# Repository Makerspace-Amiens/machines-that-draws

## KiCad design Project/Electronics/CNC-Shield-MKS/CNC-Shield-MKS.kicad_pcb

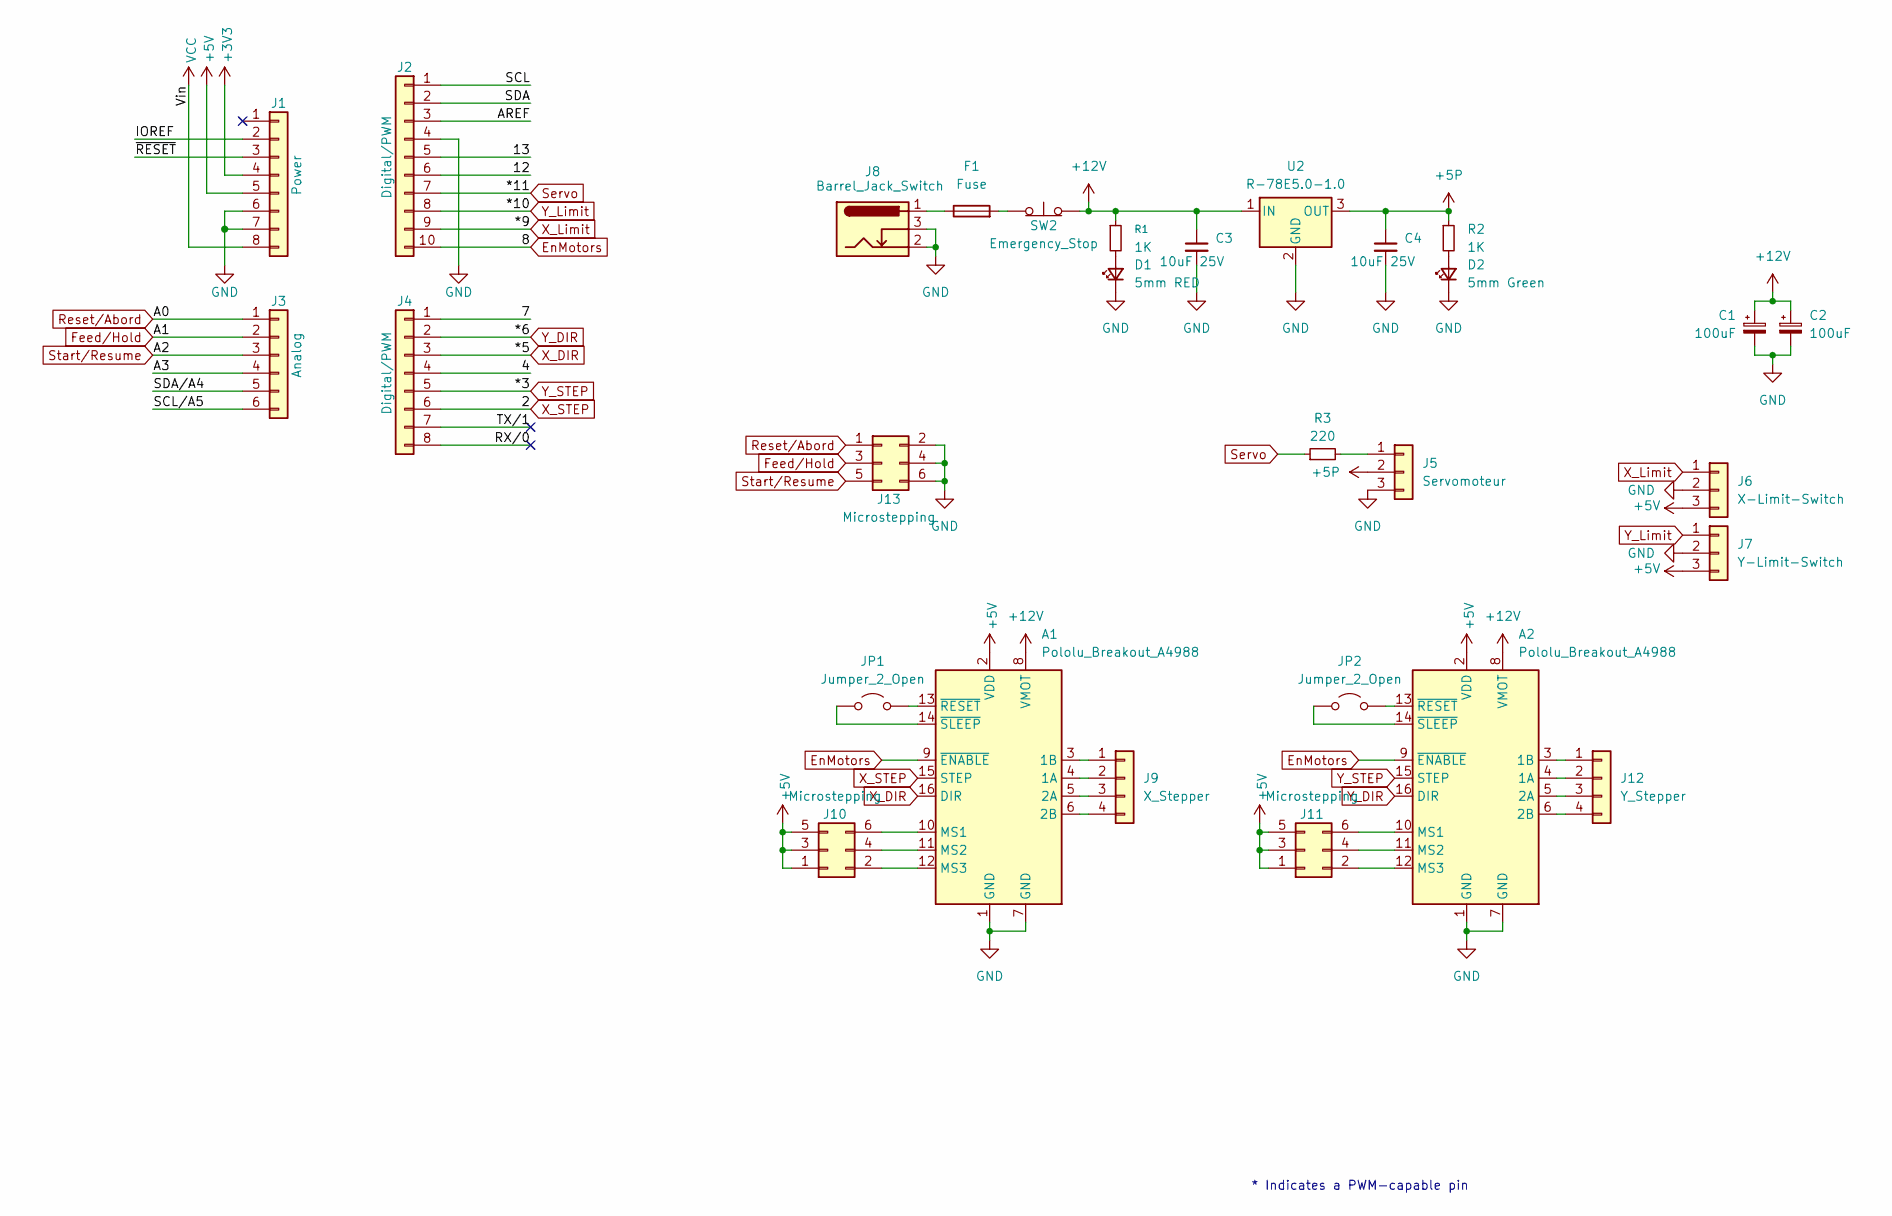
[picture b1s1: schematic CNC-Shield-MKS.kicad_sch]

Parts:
A1, A2: Pololu_Breakout_A4988; Pololu_Breakout-16_15.2x20.3mm
C1, C2: 100uF; CP_Radial_D8.0mm_P3.50mm
C3, C4: 10uF 25V; C_Disc_D6.0mm_W2.5mm_P5.00mm
D1: 5mm RED; LED_D5.0mm
D2: 5mm Green; LED_D5.0mm
F1: Fuse; Fuseholder_Blade_Mini_Keystone_3568
J1: Power; PinHeader_1x08_P2.54mm_Vertical
J2: Digital/PWM; PinHeader_1x10_P2.54mm_Vertical
J3: Analog; PinHeader_1x06_P2.54mm_Vertical
J4: Digital/PWM; PinHeader_1x08_P2.54mm_Vertical
J5: Servomoteur; PinHeader_1x03_P2.54mm_Vertical
J6: X-Limit-Switch; PinHeader_1x03_P2.54mm_Vertical
J7: Y-Limit-Switch; PinHeader_1x03_P2.54mm_Vertical
J8: Barrel_Jack_Switch; BarrelJack_Horizontal
J9: X_Stepper; PinHeader_1x04_P2.54mm_Vertical
J10, J11, J13: Microstepping; PinHeader_2x03_P2.54mm_Vertical
J12: Y_Stepper; PinHeader_1x04_P2.54mm_Vertical
JP1, JP2: Jumper_2_Open; TestPoint_2Pads_Pitch2.54mm_Drill0.8mm
R1, R2: 1K; R_Axial_DIN0204_L3.6mm_D1.6mm_P5.08mm_Horizontal
R3: 220; R_Axial_DIN0204_L3.6mm_D1.6mm_P5.08mm_Horizontal
SW2: Emergency_Stop; TerminalBlock_Phoenix_MKDS-1,5-2_1x02_P5.00mm_Horizontal
U2: R-78E5.0-1.0; Converter_DCDC_RECOM_R-78E-0.5_THT

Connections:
+3V3: J1.4
+5P: C4.1, J5.2, R2.1, U2.3 (OUT)
+5V: A1.2 (VDD), A2.2 (VDD), J1.5, J6.3, J7.3, J10.1, J10.3, J10.5, J11.1, J11.3, J11.5
+12V: A1.8 (VMOT), A2.8 (VMOT), C1.1, C2.1, C3.1, R1.1, SW2.1 (A), U2.1 (IN)
/4: J4.4
/7: J4.1
/12: J2.6
/13: J2.5
/A3: J3.4
/AREF: J2.3
/IOREF: J1.2
/RX/0: J4.8
/SCL: J2.1
/SCL/A5: J3.6
/SDA: J2.2
/SDA/A4: J3.5
/TX/1: J4.7
/~RESET: J1.3
EnMotors: A1.9 (~ENABLE), A2.9 (~ENABLE), J2.10
Feed/Hold: J3.2, J13.3
GND: A1.1 (GND), A1.7 (GND), A2.1 (GND), A2.7 (GND), C1.2, C2.2, C3.2, C4.2, D1.1 (K), D2.1 (K), J1.6, J1.7, J2.4, J5.3, J6.2, J7.2, J8.2, J8.3, J13.2, J13.4, J13.6, U2.2 (GND)
unnamed: A1.4 (1A), J9.2
unnamed: A1.3 (1B), J9.1
unnamed: A1.5 (2A), J9.3
unnamed: A1.6 (2B), J9.4
unnamed: A1.10 (MS1), J10.6
unnamed: A1.11 (MS2), J10.4
unnamed: A1.12 (MS3), J10.2
unnamed: A1.13 (~RESET), JP1.2 (B)
unnamed: A1.14 (~SLEEP), JP1.1 (A)
unnamed: A2.4 (1A), J12.2
unnamed: A2.3 (1B), J12.1
unnamed: A2.5 (2A), J12.3
unnamed: A2.6 (2B), J12.4
unnamed: A2.10 (MS1), J11.6
unnamed: A2.11 (MS2), J11.4
unnamed: A2.12 (MS3), J11.2
unnamed: A2.13 (~RESET), JP2.2 (B)
unnamed: A2.14 (~SLEEP), JP2.1 (A)
unnamed: D1.2 (A), R1.2
unnamed: D2.2 (A), R2.2
unnamed: F1.1, J8.1
unnamed: J5.1, R3.2
unnamed: F1.2, SW2.2 (B)
Reset/Abord: J3.1, J13.1
Servo: J2.7, R3.1
Start/Resume: J3.3, J13.5
VCC: J1.8
X_DIR: A1.16 (DIR), J4.3
X_Limit: J2.9, J6.1
X_STEP: A1.15 (STEP), J4.6
Y_DIR: A2.16 (DIR), J4.2
Y_Limit: J2.8, J7.1
Y_STEP: A2.15 (STEP), J4.5

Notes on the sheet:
* Indicates a PWM-capable pin

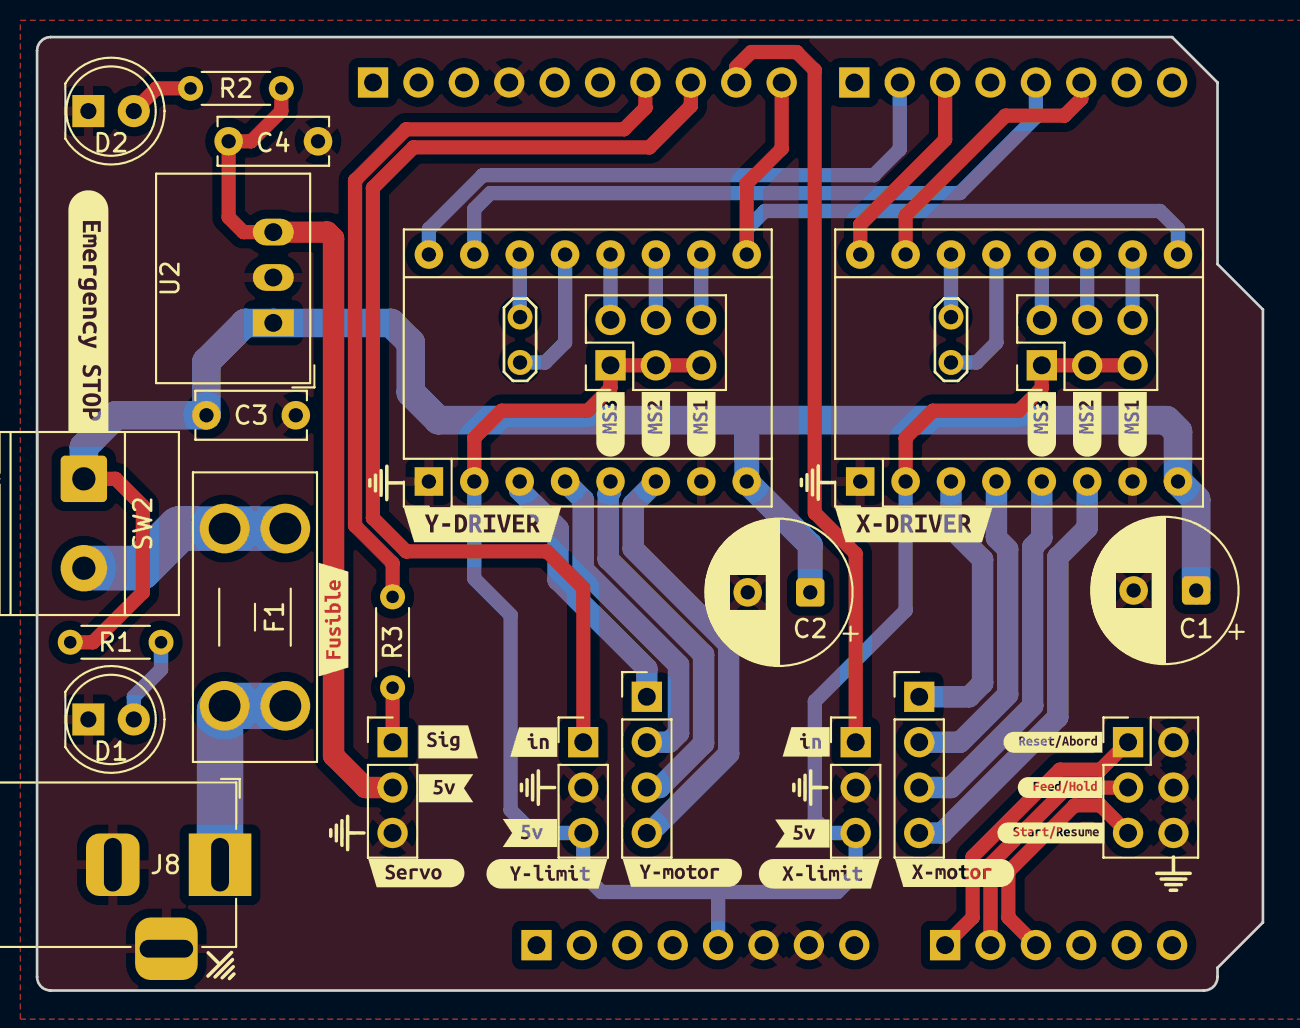
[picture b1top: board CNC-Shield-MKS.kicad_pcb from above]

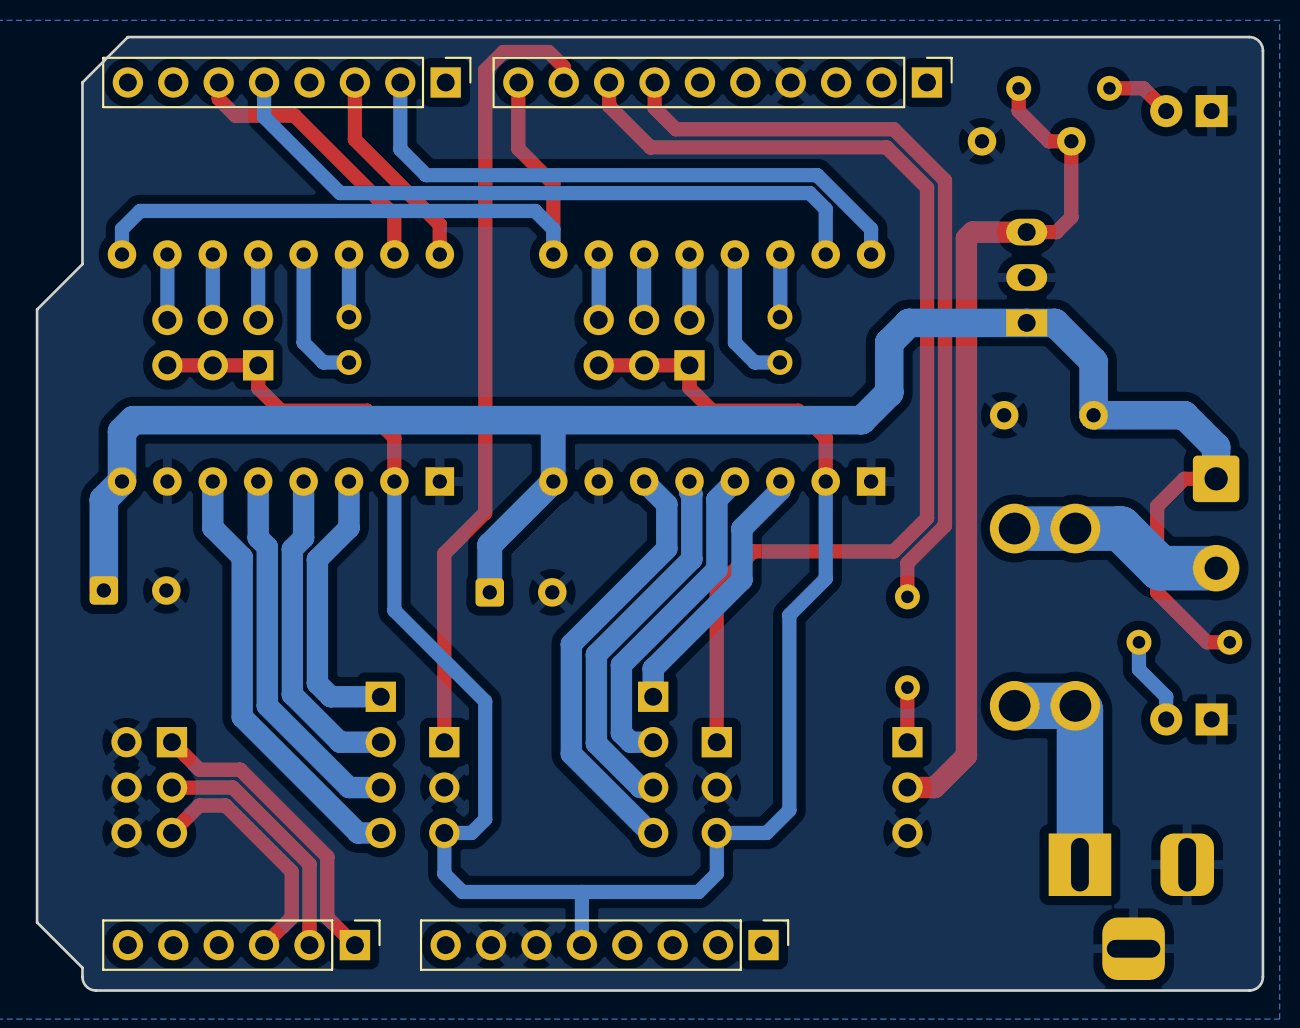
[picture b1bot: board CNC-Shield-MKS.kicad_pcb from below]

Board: 2 copper layers, 68.6 x 53.3 mm, 53 parts (4 on the bottom side), 38 nets.

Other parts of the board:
kibuzzard-68AC6E2C: G***; kibuzzard-68AC6E2C
kibuzzard-68AC6E4C: G***; kibuzzard-68AC6E4C
kibuzzard-68AC6E26: G***; kibuzzard-68AC6E26
kibuzzard-68AC6E46: G***; kibuzzard-68AC6E46
kibuzzard-68AC6EBA: G***; kibuzzard-68AC6EBA
kibuzzard-68AC6EE0: G***; kibuzzard-68AC6EE0
kibuzzard-68AC6EF6, kibuzzard-68AC6EF6#2: G***; kibuzzard-68AC6EF6
kibuzzard-68AC6F3F, kibuzzard-68AC6F3F#2: G***; kibuzzard-68AC6F3F
kibuzzard-68AC6F8C: G***; kibuzzard-68AC6F8C
kibuzzard-68AC6F9A: G***; kibuzzard-68AC6F9A
kibuzzard-68AC6F25: G***; kibuzzard-68AC6F25
kibuzzard-68AC6F70: G***; kibuzzard-68AC6F70
kibuzzard-68AC6FF4: G***; kibuzzard-68AC6FF4
kibuzzard-68AC71B3: G***; kibuzzard-68AC71B3
kibuzzard-68AC7005: G***; kibuzzard-68AC7005
kibuzzard-68AC7035, kibuzzard-68AC7035#2: G***; kibuzzard-68AC7035
kibuzzard-68AC7044, kibuzzard-68AC7044#2: G***; kibuzzard-68AC7044
kibuzzard-68AC7048, kibuzzard-68AC7048#2: G***; kibuzzard-68AC7048
kibuzzard-68AC7082: G***; kibuzzard-68AC7082

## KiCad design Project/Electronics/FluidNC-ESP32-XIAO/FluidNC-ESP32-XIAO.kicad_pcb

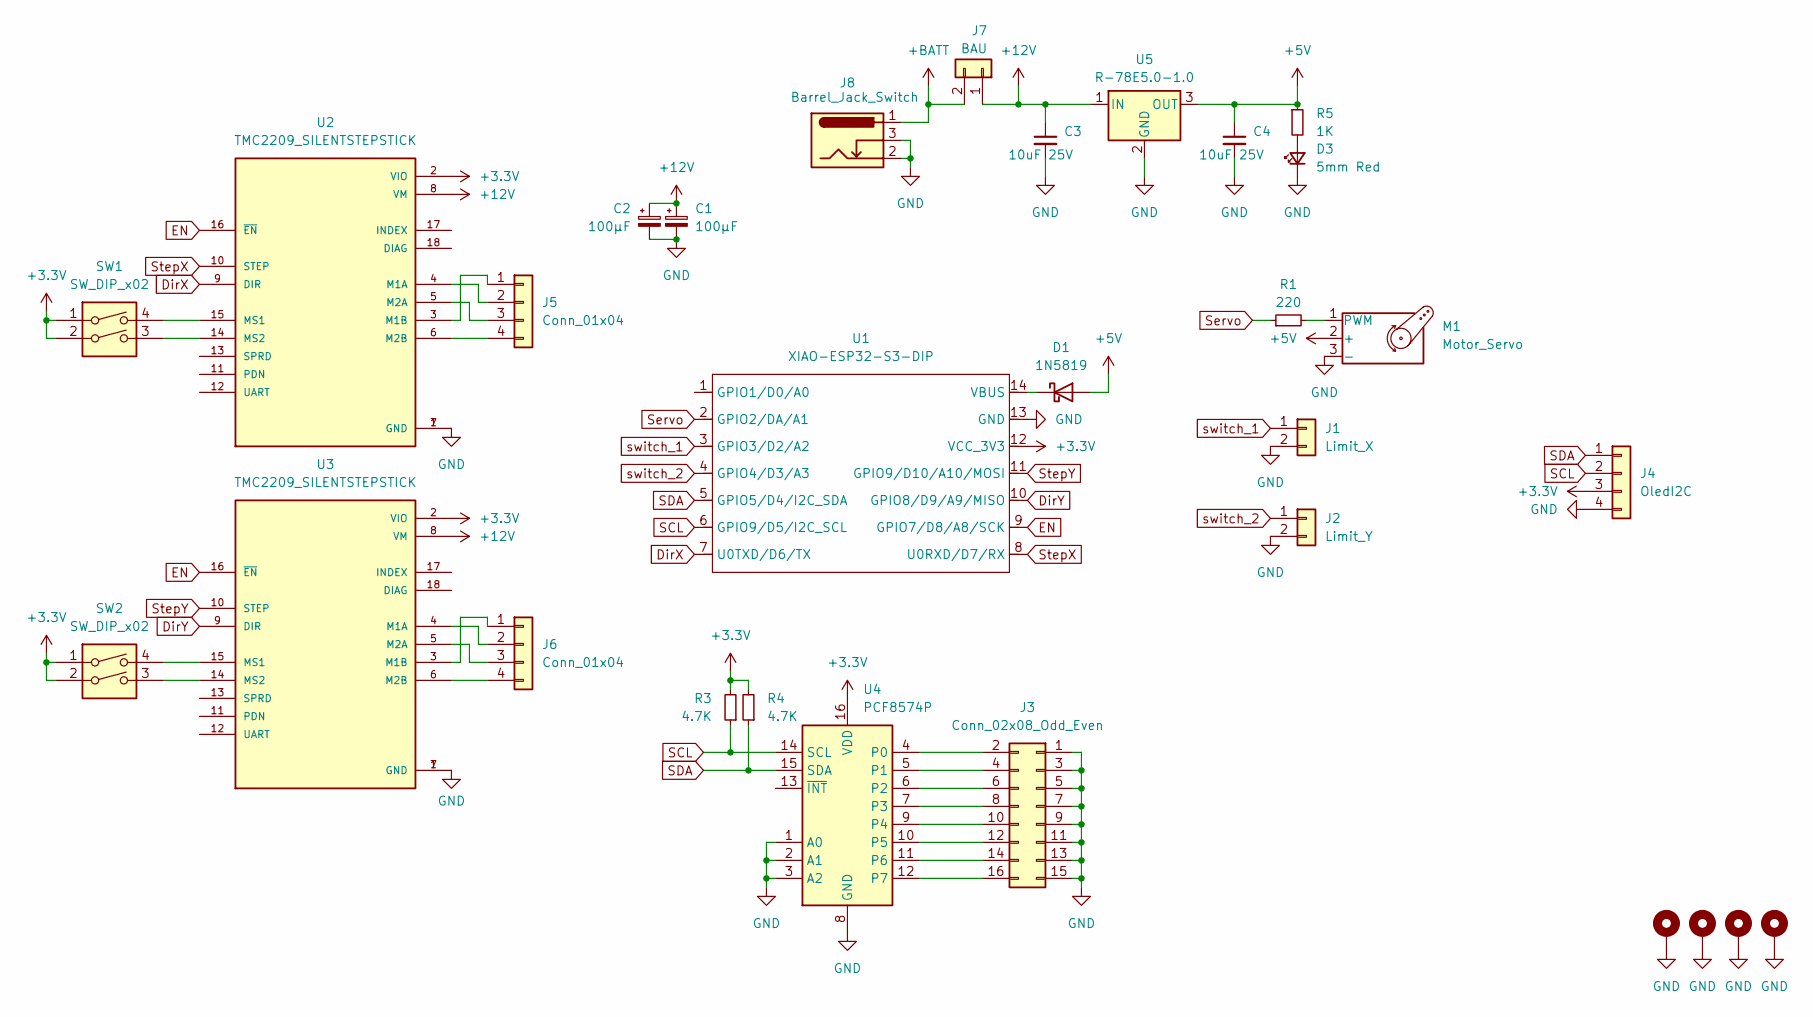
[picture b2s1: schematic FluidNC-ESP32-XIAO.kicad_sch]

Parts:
C1, C2: 100µF; CP_Radial_D10.0mm_P5.00mm
C3, C4: 10uF 25V; C_Disc_D6.0mm_W2.5mm_P5.00mm
D1: 1N5819; D_A-405_P10.16mm_Horizontal
D3: 5mm Red; LED_D5.0mm
H1, H2, H3, H4: MountingHole_Pad; MountingHole_3.2mm_M3_Pad_Via
J1: Limit_X; Molex_KK-254_AE-6410-02A_1x02_P2.54mm_Vertical
J2: Limit_Y; Molex_KK-254_AE-6410-02A_1x02_P2.54mm_Vertical
J3: Conn_02x08_Odd_Even; PinHeader_2x08_P2.54mm_Vertical
J4: OledI2C; PinSocket_1x04_P2.54mm_Vertical
J5, J6: Conn_01x04; Molex_KK-254_AE-6410-04A_1x04_P2.54mm_Vertical
J7: BAU; Molex_KK-254_AE-6410-02A_1x02_P2.54mm_Vertical
J8: Barrel_Jack_Switch; BarrelJack_Horizontal
M1: Motor_Servo; PinHeader_1x03_P2.54mm_Vertical
R1: 220; R_Axial_DIN0204_L3.6mm_D1.6mm_P7.62mm_Horizontal
R3, R4: 4.7K; R_Axial_DIN0204_L3.6mm_D1.6mm_P7.62mm_Horizontal
R5: 1K; R_Axial_DIN0204_L3.6mm_D1.6mm_P7.62mm_Horizontal
SW1, SW2: SW_DIP_x02; SW_DIP_SPSTx02_Slide_9.78x7.26mm_W7.62mm_P2.54mm
U1: XIAO-ESP32-S3-DIP; XIAO-ESP32C6-DIP
U2, U3: TMC2209_SILENTSTEPSTICK; MODULE_TMC2209_SILENTSTEPSTICK; PARTREV 1.20
U4: PCF8574P; DIP-16_W7.62mm
U5: R-78E5.0-1.0; Converter_DCDC_RECOM_R-78E-0.5_THT

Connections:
+3.3V: J4.3, R3.2, R4.2, SW1.1, SW1.2, SW2.1, SW2.2, U1.12 (VCC_3V3), U2.2 (VIO), U3.2 (VIO), U4.16 (VDD); also elsewhere on the board
+5V: C4.1, D1.2 (A), M1.2 (+), R5.1, U5.3 (OUT)
+12V: C1.1, C2.1, C3.1, J7.1, U2.8 (VM), U3.8 (VM), U5.1 (IN)
+BATT: J7.2, J8.1
DirX: U1.7 (U0TXD/D6/TX), U2.9 (DIR)
DirY: U1.10 (GPIO8/D9/A9/MISO), U3.9 (DIR)
EN: U1.9 (GPIO7/D8/A8/SCK), U2.16 (~EN), U3.16 (~EN)
GND: C1.2, C2.2, C3.2, C4.2, D3.1 (K), H1.1, H2.1, H3.1, H4.1, J1.2, J2.2, J3.1, J3.3, J3.5, J3.7, J3.9, J3.11, J3.13, J3.15, J4.4, J8.2, J8.3, M1.3 (-), U1.13 (GND), U2.1 (GND), U2.7 (GND), U3.1 (GND), U3.7 (GND), U4.1 (A0), U4.2 (A1), U4.3 (A2), U4.8 (GND), U5.2 (GND); also elsewhere on the board
Key01: U1.1 (GPIO1/D0/A0); also elsewhere on the board
unnamed: D1.1 (K), U1.14 (VBUS)
unnamed: D3.2 (A), R5.2
unnamed: J3.2, U4.4 (P0)
unnamed: J3.4, U4.5 (P1)
unnamed: J3.6, U4.6 (P2)
unnamed: J3.8, U4.7 (P3)
unnamed: J3.10, U4.9 (P4)
unnamed: J3.12, U4.10 (P5)
unnamed: J3.14, U4.11 (P6)
unnamed: J3.16, U4.12 (P7)
unnamed: J5.1, U2.3 (M1B)
unnamed: J5.2, U2.4 (M1A)
unnamed: J5.3, U2.5 (M2A)
unnamed: J5.4, U2.6 (M2B)
unnamed: J6.1, U3.3 (M1B)
unnamed: J6.2, U3.4 (M1A)
unnamed: J6.3, U3.5 (M2A)
unnamed: J6.4, U3.6 (M2B)
unnamed: M1.1 (PWM), R1.2
unnamed: SW1.4, U2.15 (MS1)
unnamed: SW1.3, U2.14 (MS2)
unnamed: SW2.4, U3.15 (MS1)
unnamed: SW2.3, U3.14 (MS2)
Servo: R1.1, U1.2 (GPIO2/DA/A1)
StepX: U1.8 (U0RXD/D7/RX), U2.10 (STEP)
StepY: U1.11 (GPIO9/D10/A10/MOSI), U3.10 (STEP)
switch_1: J1.1, U1.3 (GPIO3/D2/A2)
switch_2: J2.1, U1.4 (GPIO4/D3/A3)

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
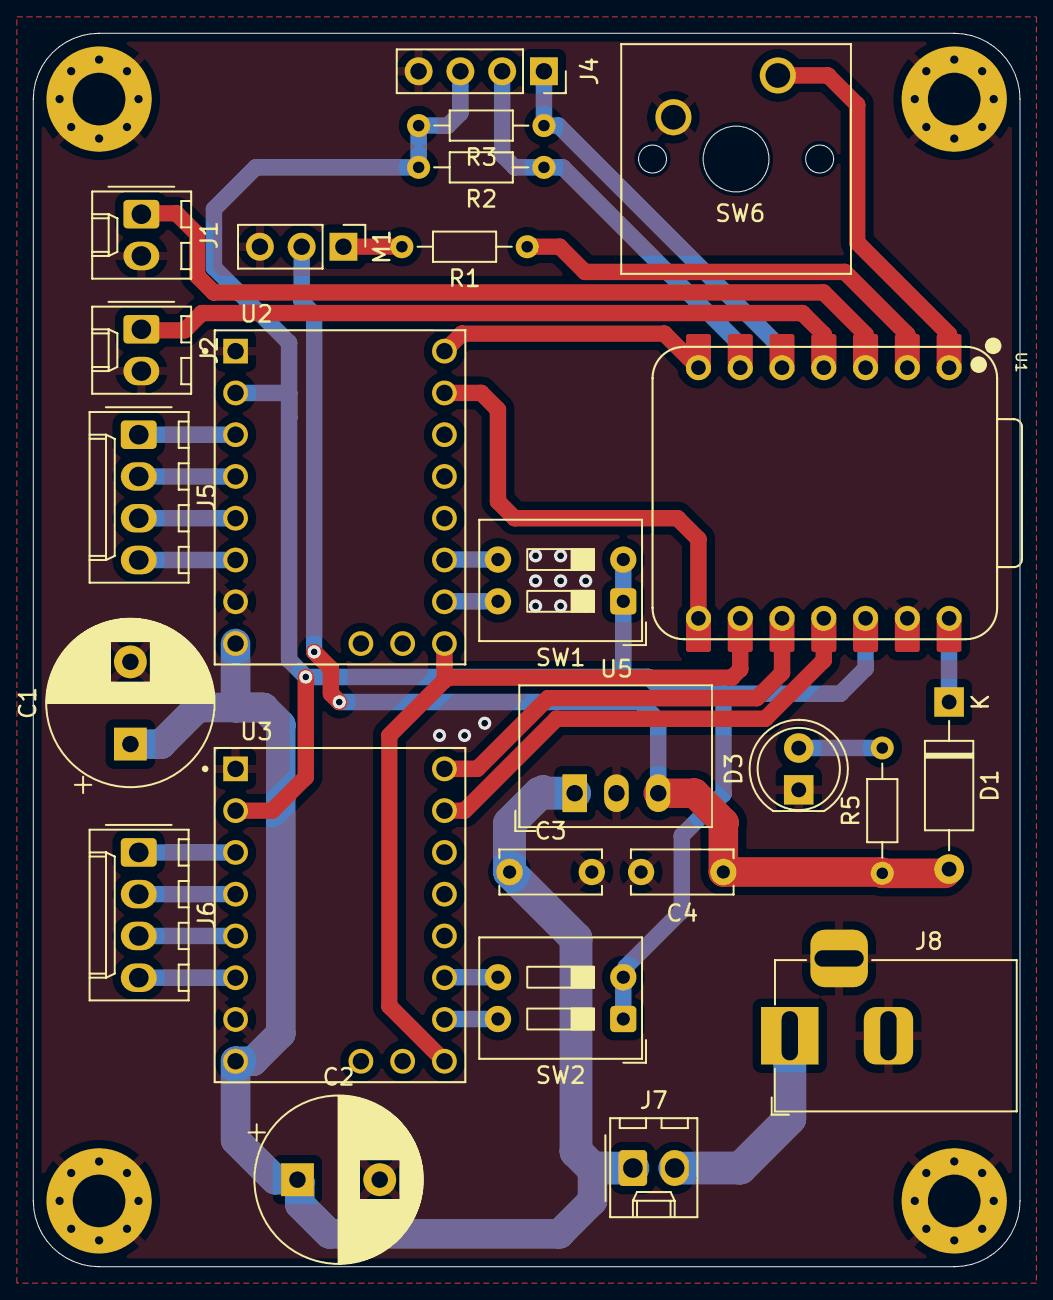
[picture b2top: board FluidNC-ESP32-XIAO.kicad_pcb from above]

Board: 2 copper layers, 60.0 x 75.0 mm, 29 parts (0 on the bottom side), 31 nets.

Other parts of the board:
R2: 4,7K; R_Axial_DIN0204_L3.6mm_D1.6mm_P7.62mm_Horizontal
SW6: CherryMX; SW_Cherry_MX_1.00u_PCB

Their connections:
+3.3V: R2.2; also elsewhere on the board
GND: SW6.2; also elsewhere on the board
Key01: SW6.1; also elsewhere on the board

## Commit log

2024-10-15 Import otto-mks template - WIP integration
2024-10-15 Update bulma-clean-theme requirement from 1.0.3 to 1.1.0
    Updates the requirements on [bulma-clean-theme](https://github.com/chrisrhymes/bulma-clean-theme) to permit the latest version.
    - [Release notes](https://github.com/chrisrhymes/bulma-clean-theme/releases)
    - [Changelog](https://github.com/chrisrhymes/bulma-clean-theme/blob/master/changelog.txt)
    - [Commits](https://github.com/chrisrhymes/bulma-clean-theme/compare/v1.0.3...v1.1.0)
    ---
    updated-dependencies:
2024-10-15 WIP - init repo
2024-10-15 new informations
2024-10-15 new doc hardware
2024-10-23 fix burger color
2024-10-24 add authors
2024-10-24 Add tutorials
2024-10-24 WIP doc - Prepare the content
2024-11-27 update informations and steps
2024-12-04 add spaceship
2024-12-04 add tuto
2024-12-04 update tuto onshape
2024-12-04 new tuto
2024-12-09 add model viewer
2024-12-09 update links - add documentation arduino IDE
2024-12-10 Added icons and modified text
2024-12-10 Resized and recolored icons
2024-12-10 fix typo
2024-12-11 update with craft-the-docs
2024-12-11 add daniel shiffman course
2024-12-12 add nature of code
2024-12-12 update images
2024-12-13 add onshape tuto link
2025-01-08 add fab additive
2025-01-20 Update bulma-clean-theme requirement from 1.1.0 to 1.2.0
    Updates the requirements on [bulma-clean-theme](https://github.com/chrisrhymes/bulma-clean-theme) to permit the latest version.
    - [Release notes](https://github.com/chrisrhymes/bulma-clean-theme/releases)
    - [Changelog](https://github.com/chrisrhymes/bulma-clean-theme/blob/master/changelog.txt)
    - [Commits](https://github.com/chrisrhymes/bulma-clean-theme/compare/v1.1.0...v1.2.0)
    ---
    updated-dependencies:
2025-03-18 add modal 3D
2025-03-19 add boilerplate
2025-03-21 New PCB for 2025-26
2025-04-02 Added geomerative ressource
2025-04-02 Added geomerative lib
2025-04-02 Removed geomerative lib
2025-04-02 Modified geomerative link
2025-05-07 Update bulma-clean-theme requirement from 1.2.0 to 1.2.1
    Updates the requirements on [bulma-clean-theme](https://github.com/chrisrhymes/bulma-clean-theme) to permit the latest version.
    - [Release notes](https://github.com/chrisrhymes/bulma-clean-theme/releases)
    - [Changelog](https://github.com/chrisrhymes/bulma-clean-theme/blob/master/changelog.txt)
    - [Commits](https://github.com/chrisrhymes/bulma-clean-theme/compare/v1.2.0...v1.2.1)
    ---
    updated-dependencies:
2025-05-14 Create Board - WIP
2025-05-14 WIP - ESP32-S3 is not compatible with fluidnc
2025-06-04 Update bulma-clean-theme requirement from 1.2.0 to 1.3.0
    Updates the requirements on [bulma-clean-theme](https://github.com/chrisrhymes/bulma-clean-theme) to permit the latest version.
    - [Release notes](https://github.com/chrisrhymes/bulma-clean-theme/releases)
    - [Changelog](https://github.com/chrisrhymes/bulma-clean-theme/blob/master/changelog.txt)
    - [Commits](https://github.com/chrisrhymes/bulma-clean-theme/compare/v1.2.0...v1.3.0)
    ---
    updated-dependencies:
2025-08-22 new cnc shield MKS
2025-12-08 Modified onshape document init
2025-12-08 Fixed context error
2026-01-07 Update bulma-clean-theme requirement from 1.2.0 to 1.3.1
    Updates the requirements on [bulma-clean-theme](https://github.com/chrisrhymes/bulma-clean-theme) to permit the latest version.
    - [Release notes](https://github.com/chrisrhymes/bulma-clean-theme/releases)
    - [Changelog](https://github.com/chrisrhymes/bulma-clean-theme/blob/master/changelog.txt)
    - [Commits](https://github.com/chrisrhymes/bulma-clean-theme/compare/v1.2.0...v1.3.1)
    ---
    updated-dependencies:
2026-01-14 Fixed Hardware home callout
2026-02-20 Added new servo calibration tutorial
2026-02-26 Finished servo calibration tutorial
2026-02-26 Fixed line return error
2026-03-20 Added That Creative Code Page to software ressources
